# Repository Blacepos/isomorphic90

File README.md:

# Isomorphic 90: A Generic Keyboard and MIDI Controller
This project is licensed under the GNU GPLv3.

This is a prototype for a future larger board.

## Features
- 90 hex-shaped velocity-sensitive keys
- Per-key RGB
- QMK compatible

## Technical
- 180 switches
- MCU: STM32F405ZGT
- LED driver: IS313741A
- RGB matrix uses external 5V power. This might not be necessary here, but will be in the larger board.

You can view the PCBs and schematics on kicanvas.org:
- [board1](https://kicanvas.org/?github=https%3A%2F%2Fgithub.com%2FBlacepos%2Fisomorphic90%2Ftree%2Fmain%2Fboard1)
- [board2](https://kicanvas.org/?github=https%3A%2F%2Fgithub.com%2FBlacepos%2Fisomorphic90%2Ftree%2Fmain%2Fboard2)

## Status
Both PCBs are nearing completion. Firmware code will be added here when it is time to implement.

## Images
Board1

Board2

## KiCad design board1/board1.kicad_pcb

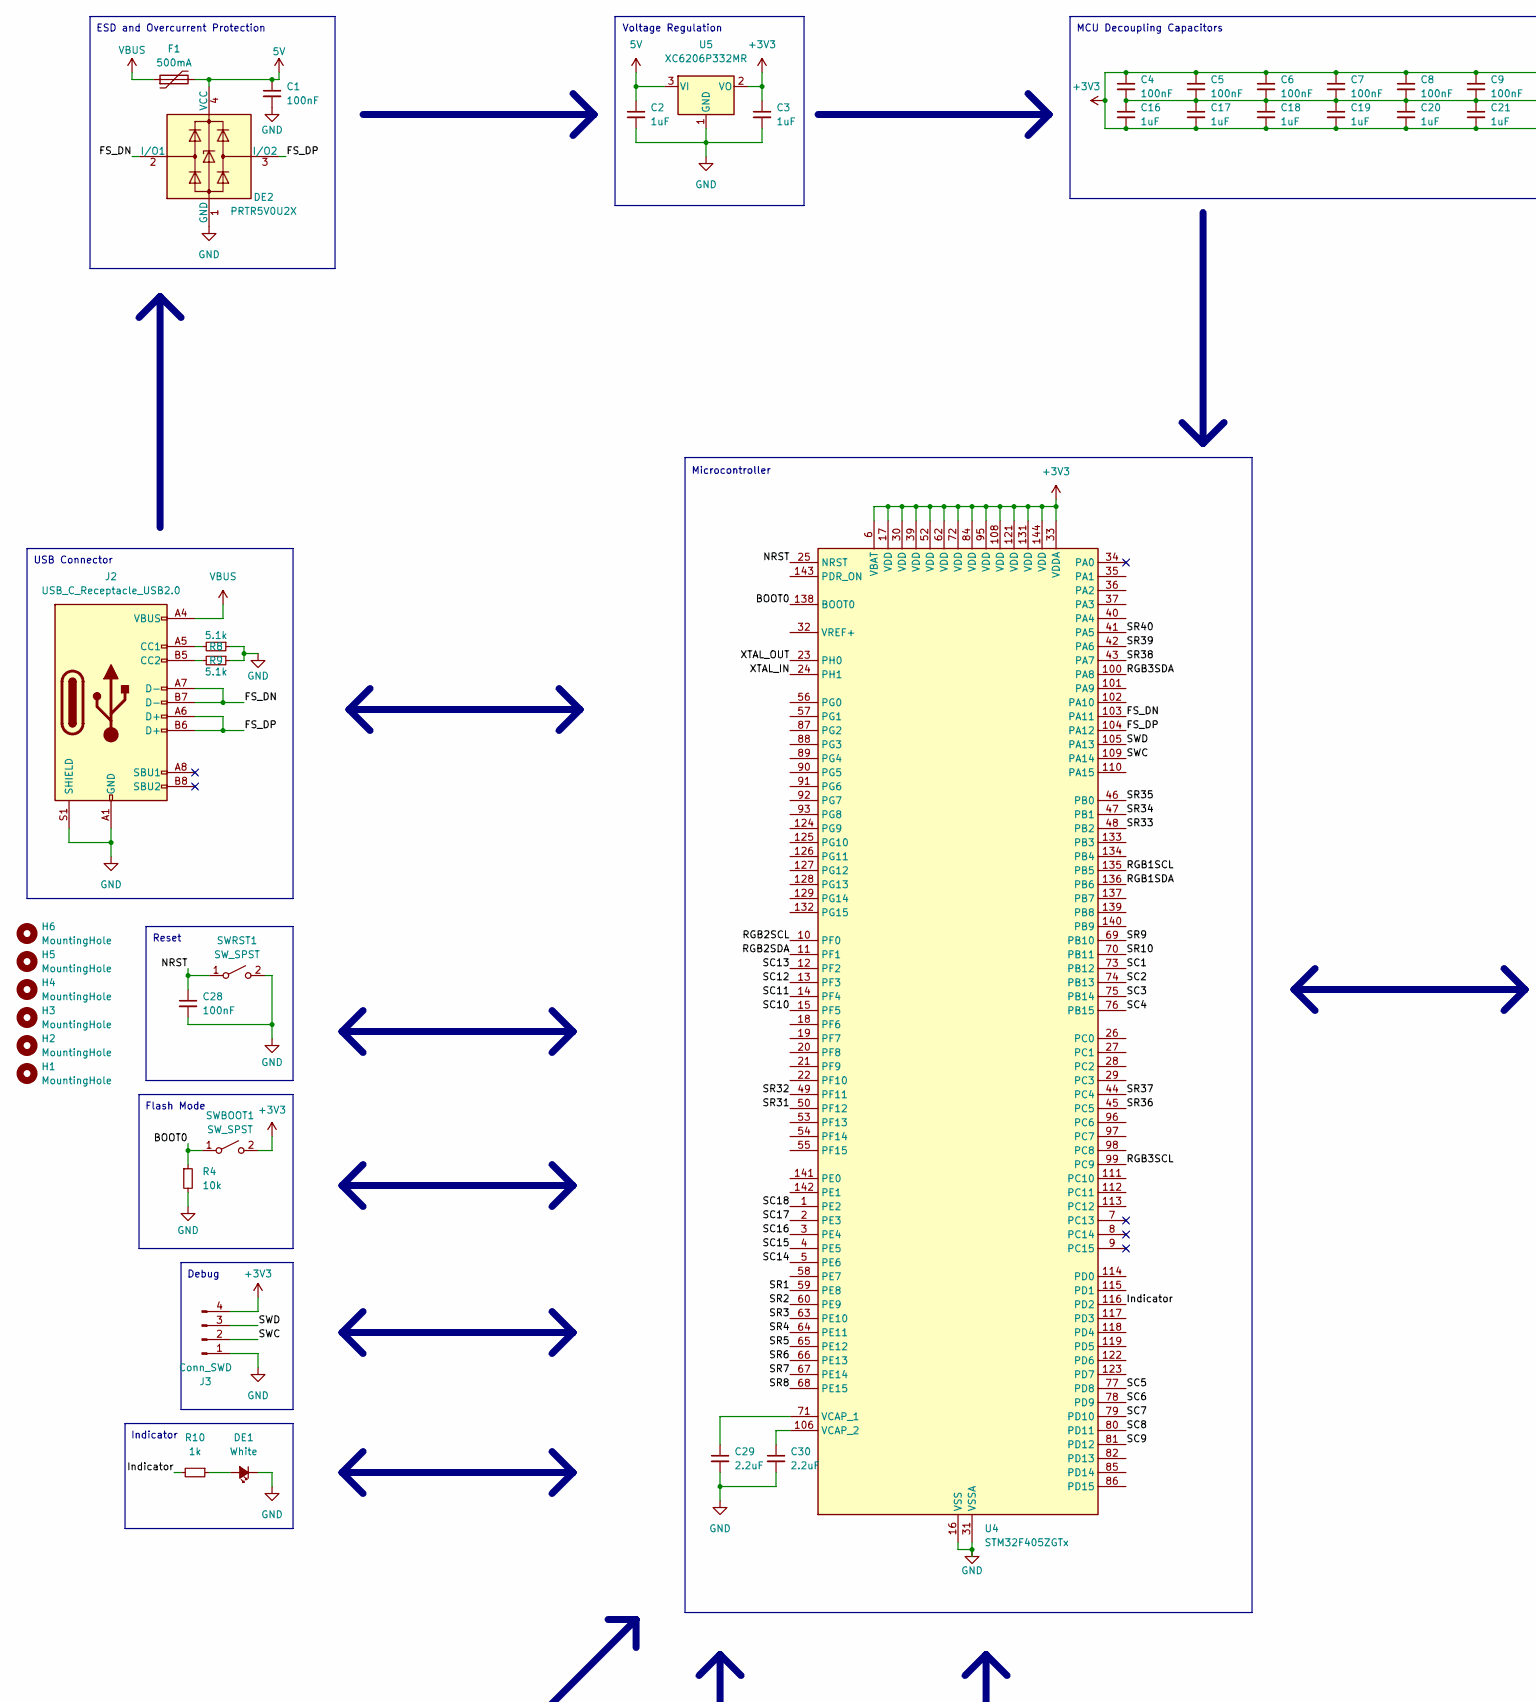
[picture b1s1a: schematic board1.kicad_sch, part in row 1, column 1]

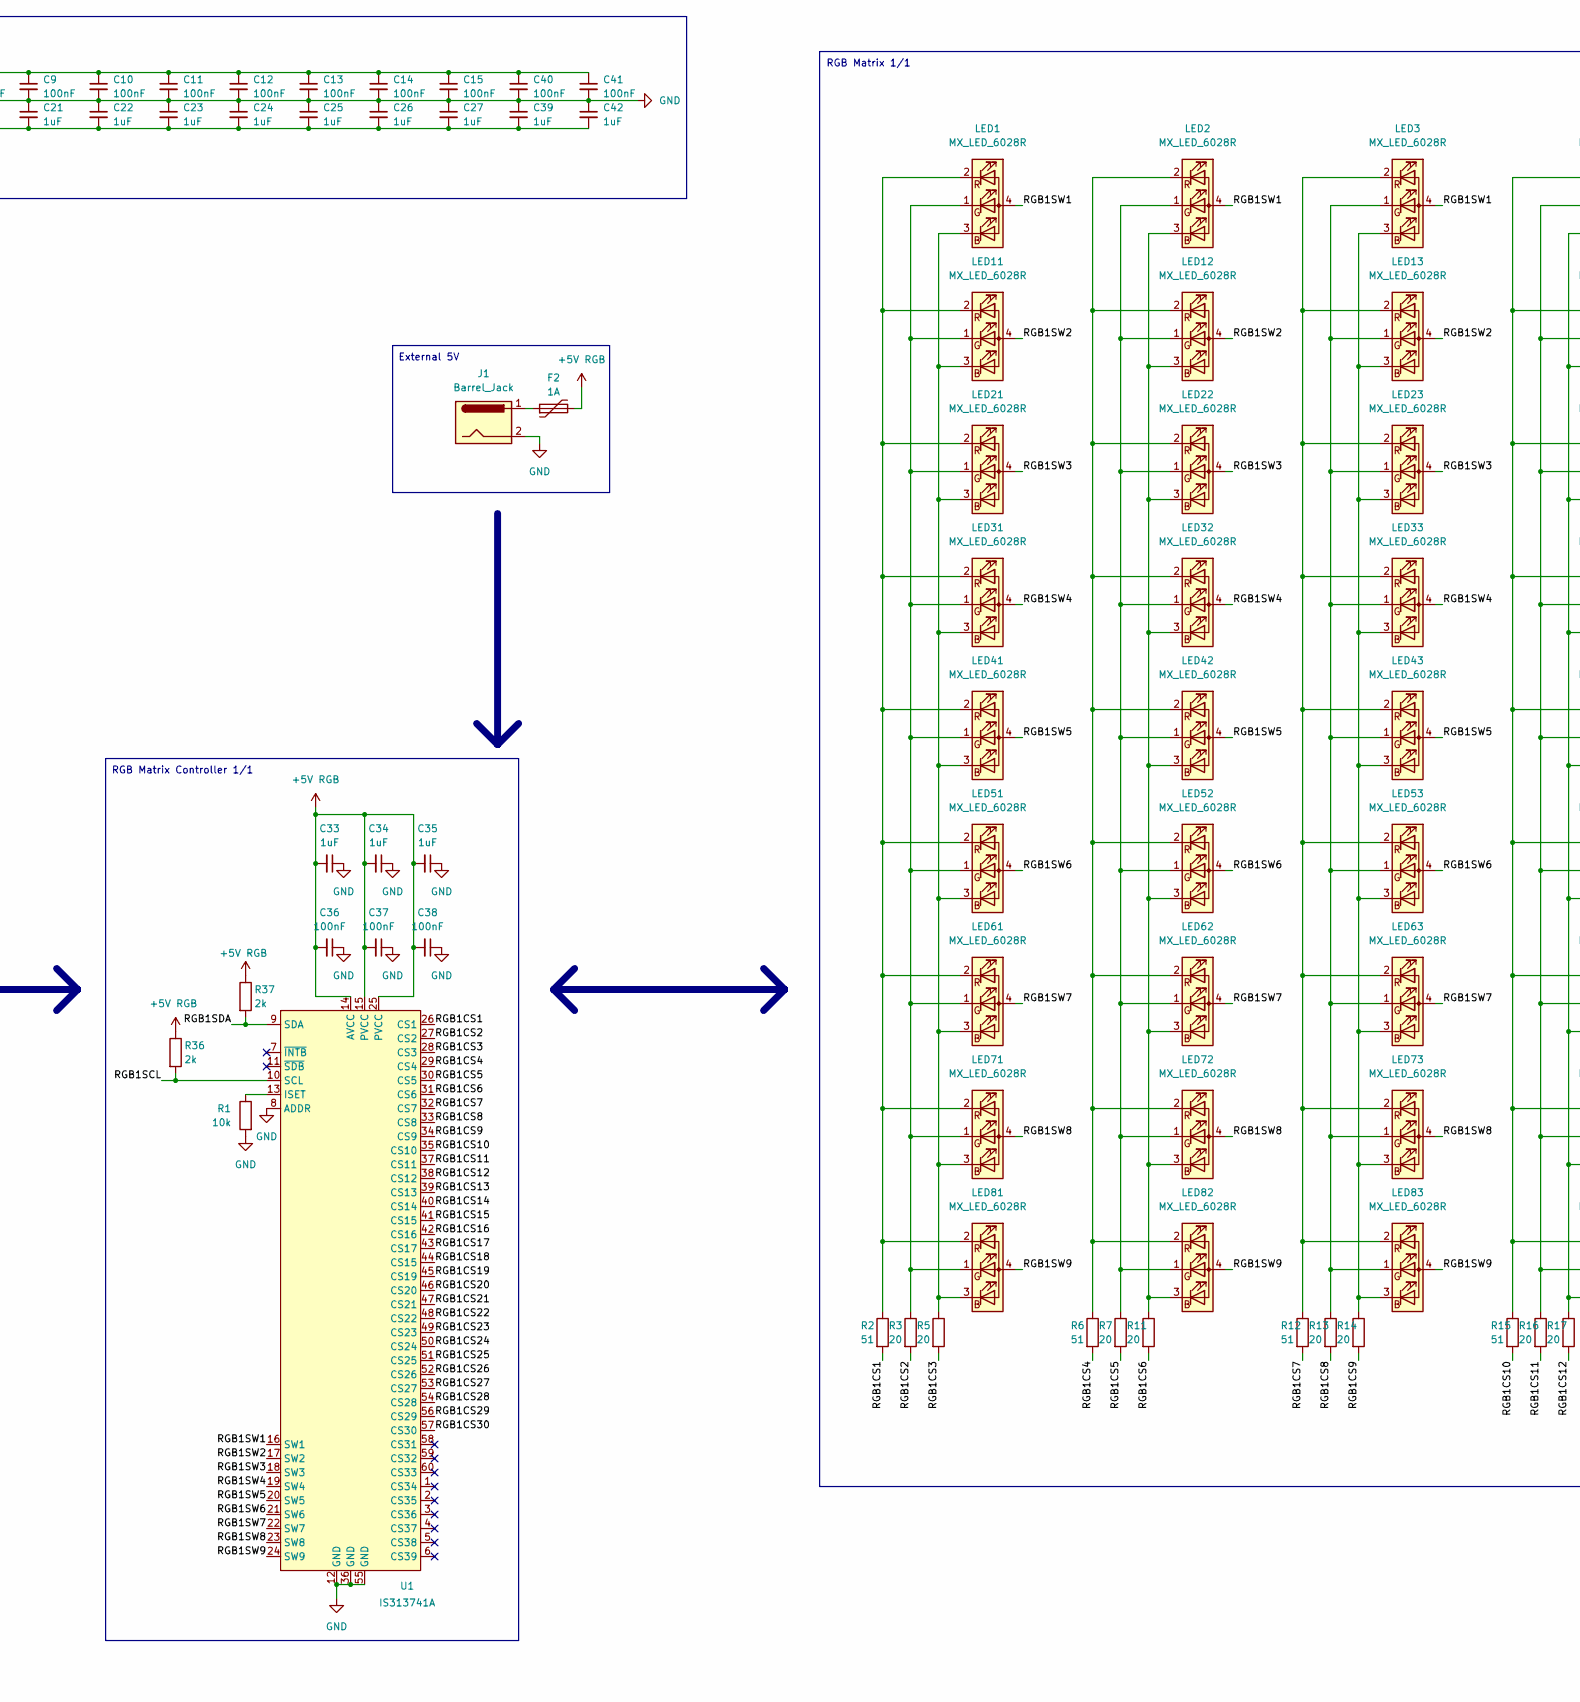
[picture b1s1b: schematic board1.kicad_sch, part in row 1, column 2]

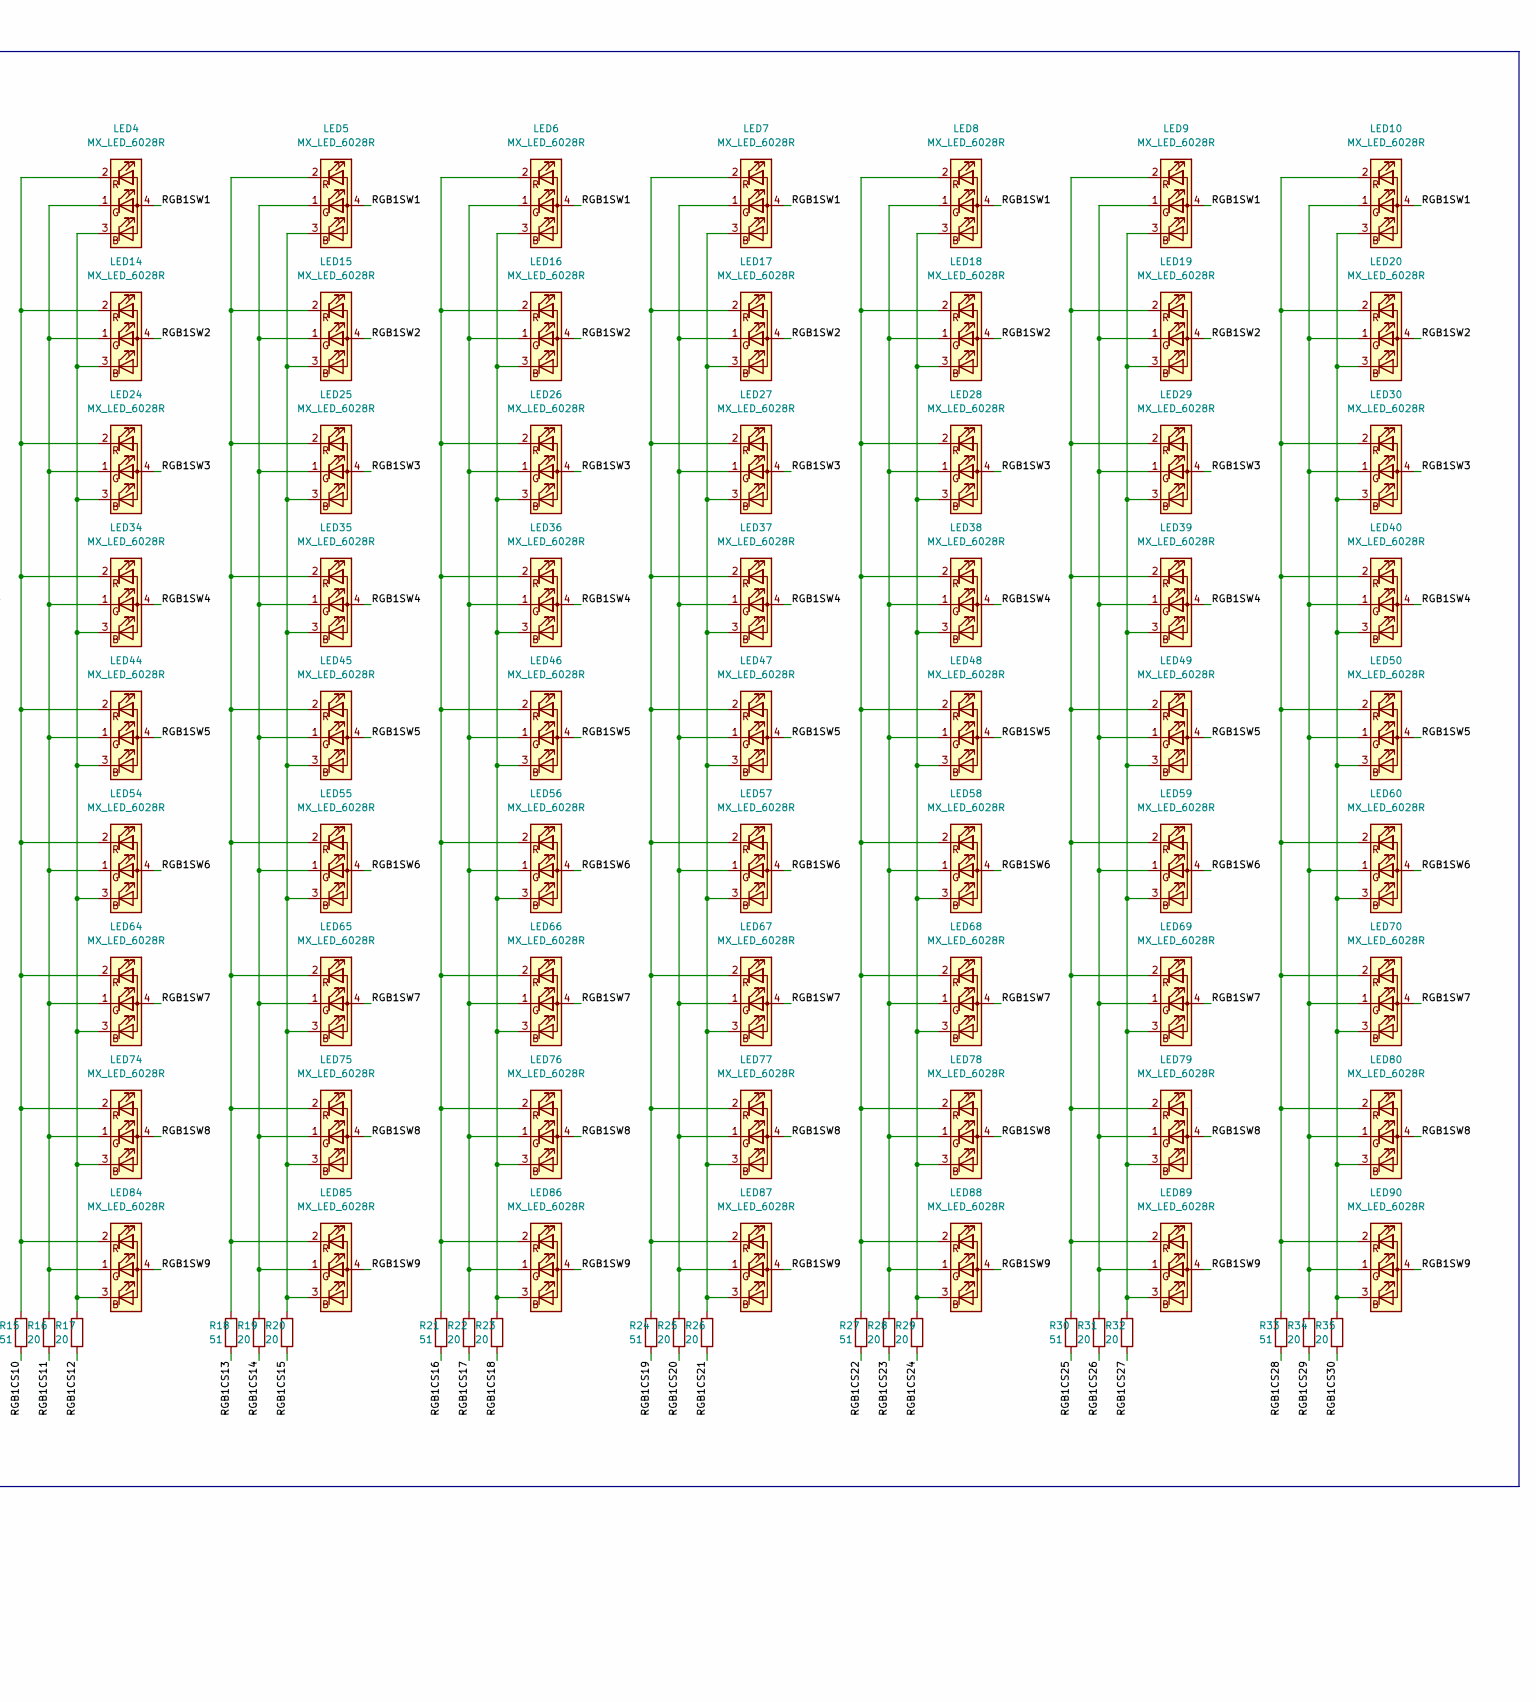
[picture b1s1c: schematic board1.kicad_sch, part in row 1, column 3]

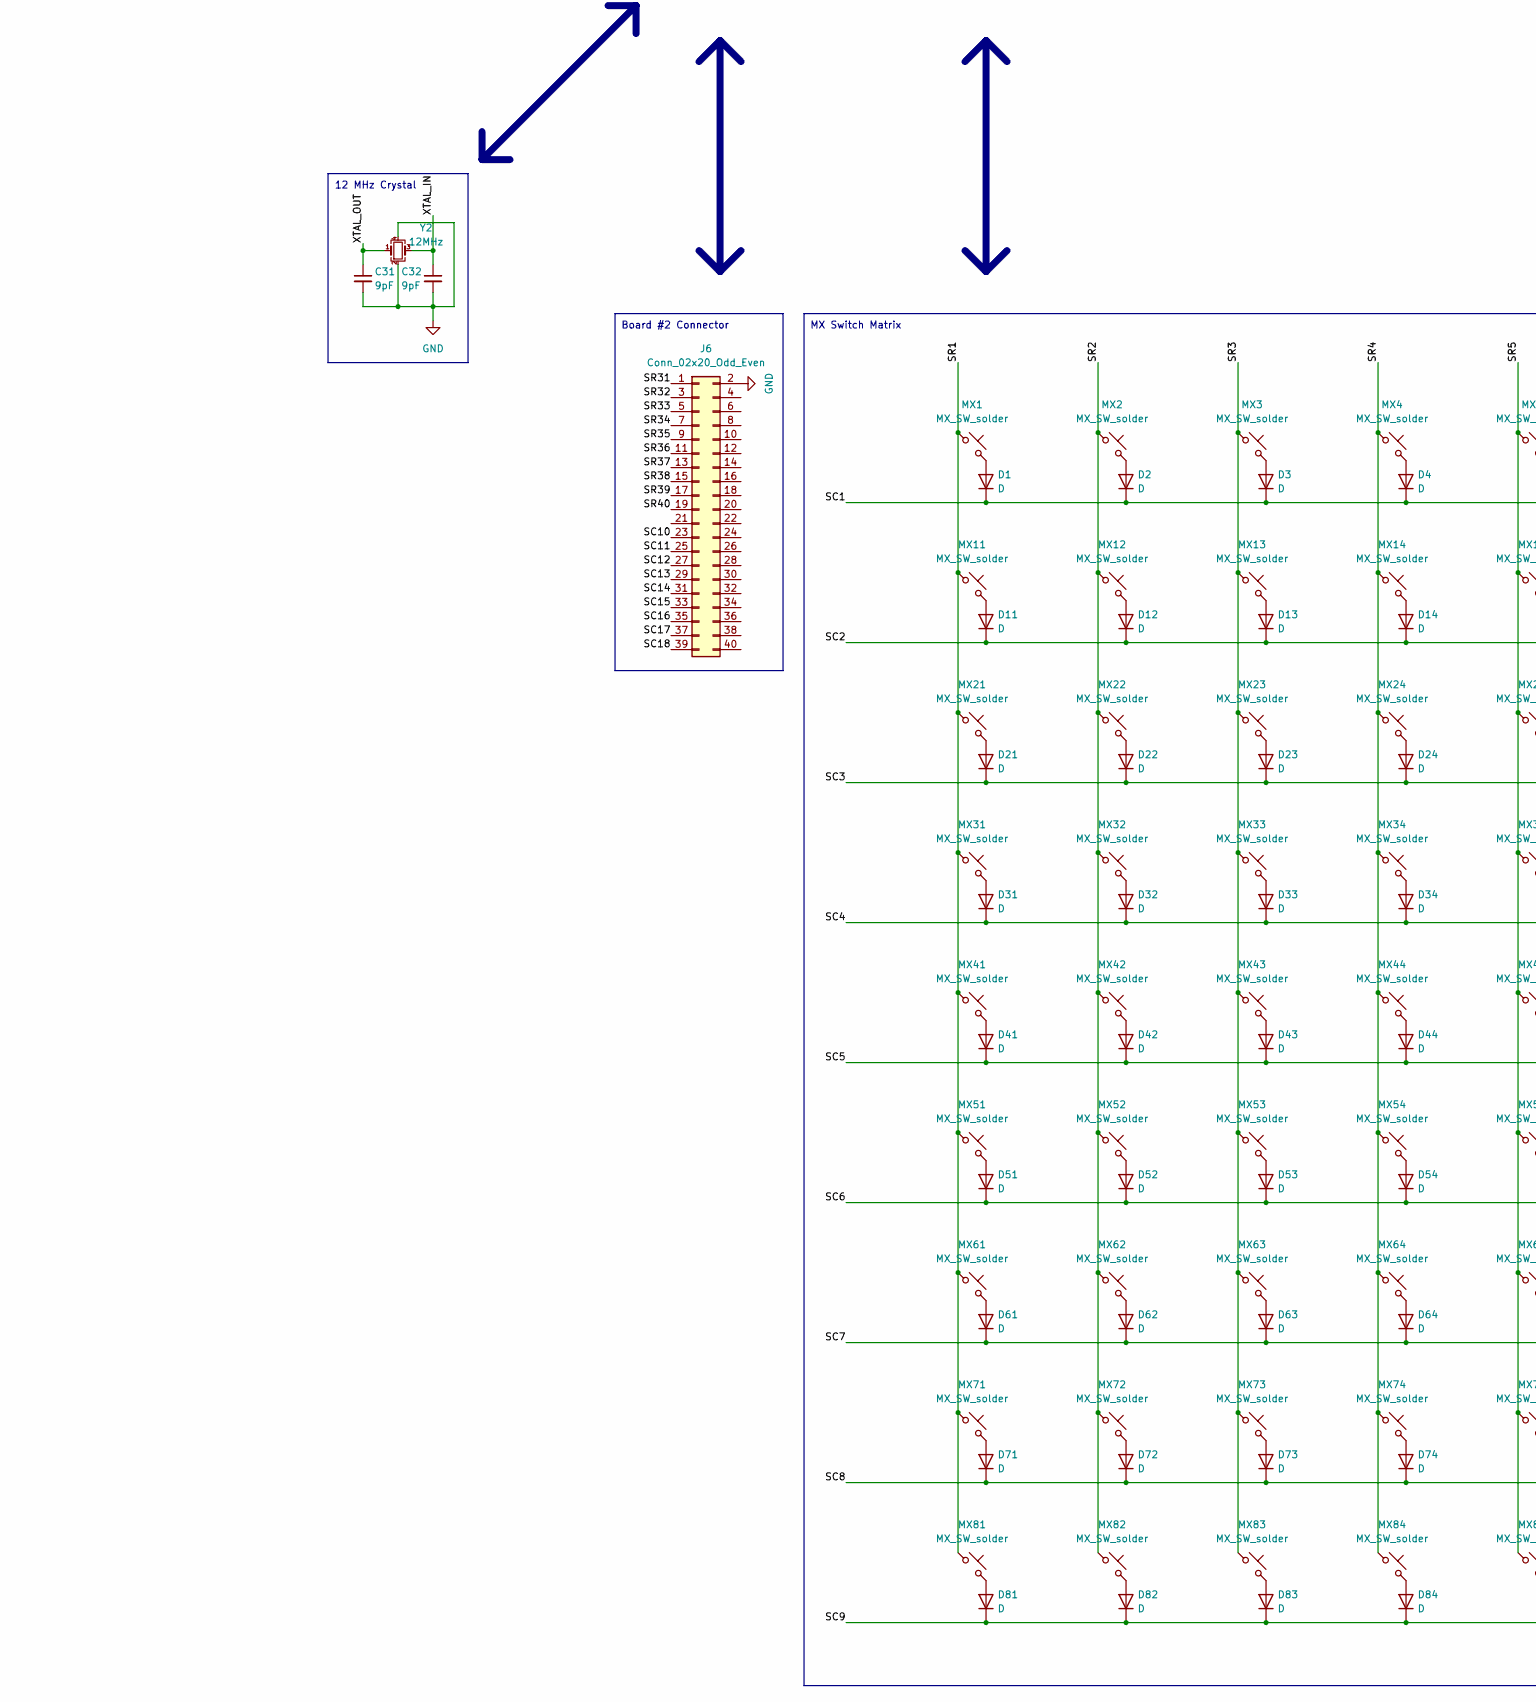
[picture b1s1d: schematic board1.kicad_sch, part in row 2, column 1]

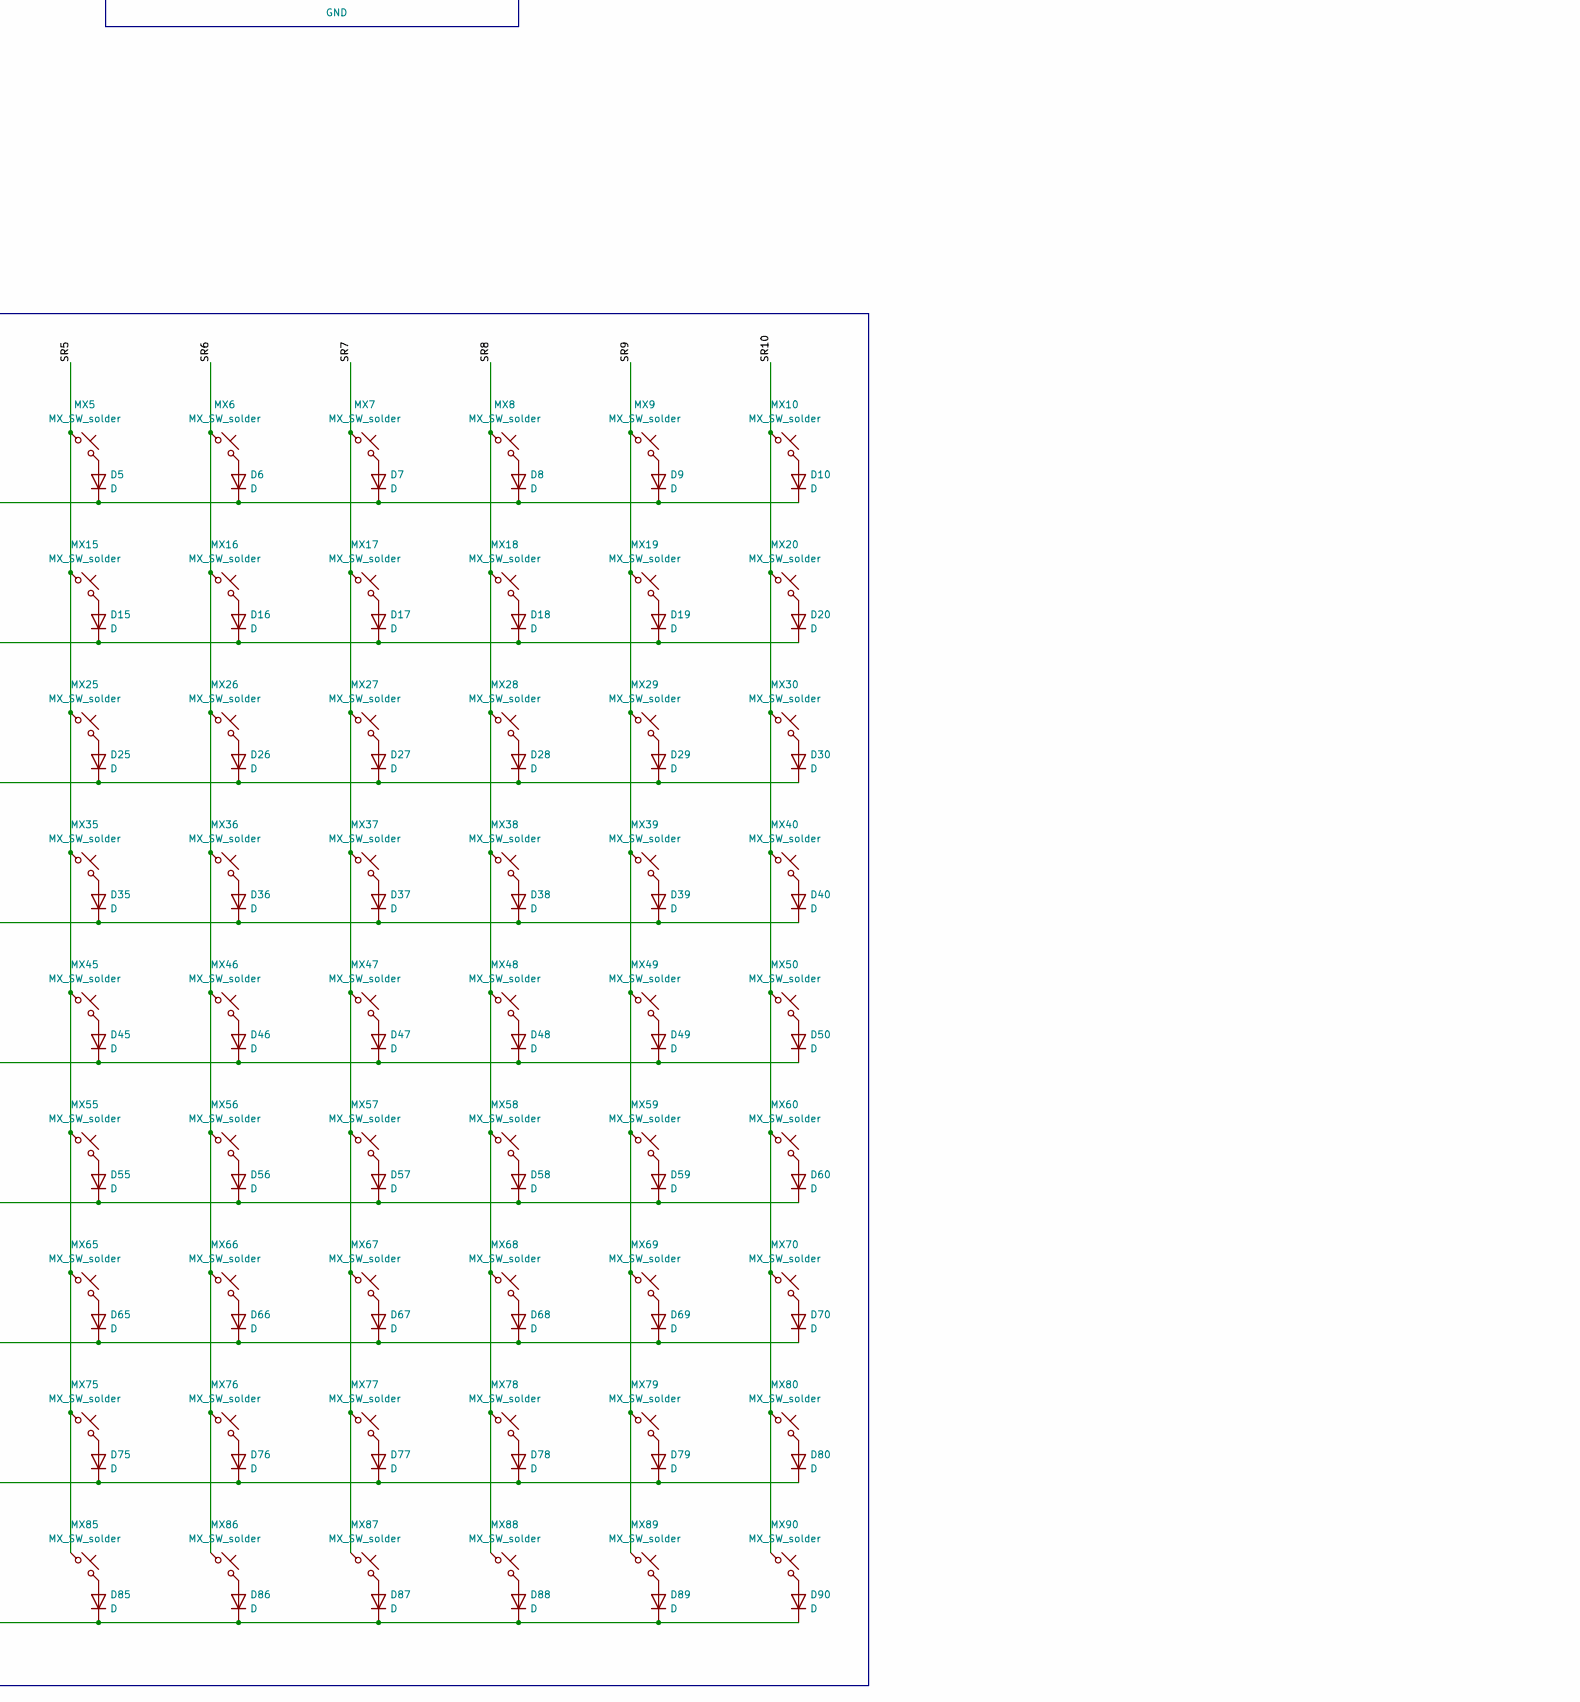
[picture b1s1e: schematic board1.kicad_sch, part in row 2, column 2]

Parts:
C1, C4, C5, C6, C7, C8, C9, C10, C11, C12, C13, C14, C15, C40, C41: 100nF; C_0603_1608Metric
C2, C3, C16, C17, C18, C19, C20, C21, C22, C23, C24, C25, C26, C27, C39, C42: 1uF; C_0603_1608Metric
C28, C36, C37, C38: 100nF; C_0402_1005Metric
C29, C30: 2.2uF; C_0603_1608Metric
C31, C32: 9pF; C_0402_1005Metric
C33, C34, C35: 1uF; C_0402_1005Metric
D1, D2, D3, D4, D5, D6, D7, D8, D9, D10, D11, D12, D13, D14, D15, D16, D17, D18, D19, D20, D21, D22, D23, D24, D25, D26, D27, D28, D29, D30, D31, D32, D33, D34, D35, D36, D37, D38, D39, D40, D41, D42, D43, D44, D45, D46, D47, D48, D49, D50, D51, D52, D53, D54, D55, D56, D57, D58, D59, D60, D61, D62, D63, D64, D65, D66, D67, D68, D69, D70, D71, D72, D73, D74, D75, D76, D77, D78, D79, D80, D81, D82, D83, D84, D85, D86, D87, D88, D89, D90: D; D_SOD-123
DE1: White; LED_0402_1005Metric
DE2: PRTR5V0U2X; SOT-143
F1: 500mA; Fuse_1206_3216Metric
F2: 1A; Fuse_1206_3216Metric
H1, H2, H3, H4, H5, H6: MountingHole; MountingHole_2.2mm_M2
J1: Barrel_Jack; BarrelJack_CUI_PJ-063AH_Horizontal
J2: USB_C_Receptacle_USB2.0; USB_C_Receptacle_HRO_TYPE-C-31-M-12
J3: Conn_SWD; PinHeader_1x04_P1.27mm_Vertical
J6: Conn_02x20_Odd_Even; IDC-Header_2x20_P2.54mm_Vertical
LED1, LED2, LED3, LED4, LED5, LED6, LED7, LED8, LED9, LED10, LED11, LED12, LED13, LED14, LED15, LED16, LED17, LED18, LED19, LED20, LED21, LED22, LED23, LED24, LED25, LED26, LED27, LED28, LED29, LED30, LED31, LED32, LED33, LED34, LED35, LED36, LED37, LED38, LED39, LED40, LED41, LED42, LED43, LED44, LED45, LED46, LED47, LED48, LED49, LED50, LED51, LED52, LED53, LED54, LED55, LED56, LED57, LED58, LED59, LED60, LED61, LED62, LED63, LED64, LED65, LED66, LED67, LED68, LED69, LED70, LED71, LED72, LED73, LED74, LED75, LED76, LED77, LED78, LED79, LED80, LED81, LED82, LED83, LED84, LED85, LED86, LED87, LED88, LED89, LED90: MX_LED_6028R; LED_MX_6028R_HEX_EDIT
MX1, MX2, MX3, MX4, MX5, MX6, MX7, MX8, MX9, MX10, MX11, MX12, MX13, MX14, MX15, MX16, MX17, MX18, MX19, MX20, MX21, MX22, MX23, MX24, MX25, MX26, MX27, MX28, MX29, MX30, MX31, MX32, MX33, MX34, MX35, MX36, MX37, MX38, MX39, MX40, MX41, MX42, MX43, MX44, MX45, MX46, MX47, MX48, MX49, MX50, MX51, MX52, MX53, MX54, MX55, MX56, MX57, MX58, MX59, MX60, MX61, MX62, MX63, MX64, MX65, MX66, MX67, MX68, MX69, MX70, MX71, MX72, MX73, MX74, MX75, MX76, MX77, MX78, MX79, MX80, MX81, MX82, MX83, MX84, MX85, MX86, MX87, MX88, MX89, MX90: MX_SW_solder; SW_MX_HEX_EDIT
R1, R4: 10k; R_0402_1005Metric
R2, R6, R12, R15, R18, R21, R24, R27, R30, R33: 51; R_0402_1005Metric
R3, R5, R7, R11, R13, R14, R16, R17, R19, R20, R22, R23, R25, R26, R28, R29, R31, R32, R34, R35: 20; R_0402_1005Metric
R8, R9: 5.1k; R_0402_1005Metric
R10: 1k; R_0402_1005Metric
R36, R37: 2k; R_0402_1005Metric
SWBOOT1: SW_SPST; SW_SPST_TL3342
SWRST1: SW_SPST; SW_SPST_TL3342
U1: IS313741A; QFN-60_EP_7x7_Pitch0.4mm
U4: STM32F405ZGTx; LQFP-144_20x20mm_P0.5mm
U5: XC6206P332MR; SOT-23
Y2: 12MHz; Crystal_SMD_3225-4Pin_3.2x2.5mm

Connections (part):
5V: C1.1, C2.1, DE2.4 (VCC), F1.2, U5.3 (VI)
+3V3: C3.1, C4.1, C5.1, C6.1, C7.1, C8.1, C9.1, C10.1, C11.1, C12.1, C13.1, C14.1, C15.1, C16.2, C17.2, C18.2, C19.2, C20.2, C21.2, C22.2, C23.2, C24.2, C25.2, C26.2, C27.2, C39.2, C40.1, C41.1, C42.2, J3.4, SWBOOT1.2 (B), U4.6 (VBAT), U4.17 (VDD), U4.30 (VDD), U4.33 (VDDA), U4.39 (VDD), U4.52 (VDD), U4.62 (VDD), U4.72 (VDD), U4.84 (VDD), U4.95 (VDD), U4.108 (VDD), U4.121 (VDD), U4.131 (VDD), U4.144 (VDD), U5.2 (VO)
+5V RGB: C33.2, C34.2, C35.2, C36.2, C37.2, C38.2, F2.2, R36.1, R37.1, U1.14 (AVCC), U1.15 (PVCC), U1.25 (PVCC)
/BOOT0: R4.1, SWBOOT1.1 (A), U4.138 (BOOT0)
/FS_DN: DE2.2 (I/O1), J2.A7 (D-), J2.B7 (D-), U4.103 (PA11)
/FS_DP: DE2.3 (I/O2), J2.A6 (D+), J2.B6 (D+), U4.104 (PA12)
/Indicator: R10.2, U4.116 (PD2)
/NRST: C28.1, SWRST1.1 (A), U4.25 (NRST)
/RGB1CS1: R2.2, U1.26 (CS1)
/RGB1CS2: R3.2, U1.27 (CS2)
/RGB1CS3: R5.2, U1.28 (CS3)
/RGB1CS4: R6.2, U1.29 (CS4)
/RGB1CS5: R7.2, U1.30 (CS5)
/RGB1CS6: R11.2, U1.31 (CS6)
/RGB1CS7: R12.2, U1.32 (CS7)
/RGB1CS8: R13.2, U1.33 (CS8)
/RGB1CS9: R14.2, U1.34 (CS9)
/RGB1CS10: R15.2, U1.35 (CS10)
/RGB1CS11: R16.2, U1.37 (CS11)
/RGB1CS12: R17.2, U1.38 (CS12)
/RGB1CS13: R18.2, U1.39 (CS13)
/RGB1CS14: R19.2, U1.40 (CS14)
/RGB1CS15: R20.2, U1.41 (CS15)
/RGB1CS16: R21.2, U1.42 (CS16)
/RGB1CS17: R22.2, U1.43 (CS17)
/RGB1CS18: R23.2, U1.44 (CS15)
/RGB1CS19: R24.2, U1.45 (CS19)
/RGB1CS20: R25.2, U1.46 (CS20)
/RGB1CS21: R26.2, U1.47 (CS21)
/RGB1CS22: R27.2, U1.48 (CS22)
/RGB1CS23: R28.2, U1.49 (CS23)
/RGB1CS24: R29.2, U1.50 (CS24)
/RGB1CS25: R30.2, U1.51 (CS25)
/RGB1CS26: R31.2, U1.52 (CS26)
/RGB1CS27: R32.2, U1.53 (CS27)
/RGB1CS28: R33.2, U1.54 (CS28)
/RGB1CS29: R34.2, U1.56 (CS29)
/RGB1CS30: R35.2, U1.57 (CS30)
/RGB1SCL: R36.2, U1.10 (SCL), U4.135 (PB5)
/RGB1SDA: R37.2, U1.9 (SDA), U4.136 (PB6)
/RGB1SW1: LED1.4 (A), LED2.4 (A), LED3.4 (A), LED4.4 (A), LED5.4 (A), LED6.4 (A), LED7.4 (A), LED8.4 (A), LED9.4 (A), LED10.4 (A), U1.16 (SW1)
/RGB1SW2: LED11.4 (A), LED12.4 (A), LED13.4 (A), LED14.4 (A), LED15.4 (A), LED16.4 (A), LED17.4 (A), LED18.4 (A), LED19.4 (A), LED20.4 (A), U1.17 (SW2)
/RGB1SW3: LED21.4 (A), LED22.4 (A), LED23.4 (A), LED24.4 (A), LED25.4 (A), LED26.4 (A), LED27.4 (A), LED28.4 (A), LED29.4 (A), LED30.4 (A), U1.18 (SW3)
/RGB1SW4: LED31.4 (A), LED32.4 (A), LED33.4 (A), LED34.4 (A), LED35.4 (A), LED36.4 (A), LED37.4 (A), LED38.4 (A), LED39.4 (A), LED40.4 (A), U1.19 (SW4)
/RGB1SW5: LED41.4 (A), LED42.4 (A), LED43.4 (A), LED44.4 (A), LED45.4 (A), LED46.4 (A), LED47.4 (A), LED48.4 (A), LED49.4 (A), LED50.4 (A), U1.20 (SW5)
/RGB1SW6: LED51.4 (A), LED52.4 (A), LED53.4 (A), LED54.4 (A), LED55.4 (A), LED56.4 (A), LED57.4 (A), LED58.4 (A), LED59.4 (A), LED60.4 (A), U1.21 (SW6)
/RGB1SW7: LED61.4 (A), LED62.4 (A), LED63.4 (A), LED64.4 (A), LED65.4 (A), LED66.4 (A), LED67.4 (A), LED68.4 (A), LED69.4 (A), LED70.4 (A), U1.22 (SW7)
/RGB1SW8: LED71.4 (A), LED72.4 (A), LED73.4 (A), LED74.4 (A), LED75.4 (A), LED76.4 (A), LED77.4 (A), LED78.4 (A), LED79.4 (A), LED80.4 (A), U1.23 (SW8)
/RGB1SW9: LED81.4 (A), LED82.4 (A), LED83.4 (A), LED84.4 (A), LED85.4 (A), LED86.4 (A), LED87.4 (A), LED88.4 (A), LED89.4 (A), LED90.4 (A), U1.24 (SW9)
/RGB2SCL: U4.10 (PF0)
/RGB2SDA: U4.11 (PF1)
/RGB3SCL: U4.99 (PC9)
/RGB3SDA: U4.100 (PA8)
/SC1: D1.1 (K), D2.1 (K), D3.1 (K), D4.1 (K), D5.1 (K), D6.1 (K), D7.1 (K), D8.1 (K), D9.1 (K), D10.1 (K), U4.73 (PB12)
/SC2: D11.1 (K), D12.1 (K), D13.1 (K), D14.1 (K), D15.1 (K), D16.1 (K), D17.1 (K), D18.1 (K), D19.1 (K), D20.1 (K), U4.74 (PB13)
/SC3: D21.1 (K), D22.1 (K), D23.1 (K), D24.1 (K), D25.1 (K), D26.1 (K), D27.1 (K), D28.1 (K), D29.1 (K), D30.1 (K), U4.75 (PB14)
/SC4: D31.1 (K), D32.1 (K), D33.1 (K), D34.1 (K), D35.1 (K), D36.1 (K), D37.1 (K), D38.1 (K), D39.1 (K), D40.1 (K), U4.76 (PB15)
/SC5: D41.1 (K), D42.1 (K), D43.1 (K), D44.1 (K), D45.1 (K), D46.1 (K), D47.1 (K), D48.1 (K), D49.1 (K), D50.1 (K), U4.77 (PD8)
/SC6: D51.1 (K), D52.1 (K), D53.1 (K), D54.1 (K), D55.1 (K), D56.1 (K), D57.1 (K), D58.1 (K), D59.1 (K), D60.1 (K), U4.78 (PD9)
/SC7: D61.1 (K), D62.1 (K), D63.1 (K), D64.1 (K), D65.1 (K), D66.1 (K), D67.1 (K), D68.1 (K), D69.1 (K), D70.1 (K), U4.79 (PD10)
/SC8: D71.1 (K), D72.1 (K), D73.1 (K), D74.1 (K), D75.1 (K), D76.1 (K), D77.1 (K), D78.1 (K), D79.1 (K), D80.1 (K), U4.80 (PD11)
/SC9: D81.1 (K), D82.1 (K), D83.1 (K), D84.1 (K), D85.1 (K), D86.1 (K), D87.1 (K), D88.1 (K), D89.1 (K), D90.1 (K), U4.81 (PD12)
/SC10: J6.23, U4.15 (PF5)
/SC11: J6.25, U4.14 (PF4)
/SC12: J6.27, U4.13 (PF3)
/SC13: J6.29, U4.12 (PF2)
/SC14: J6.31, U4.5 (PE6)
/SC15: J6.33, U4.4 (PE5)
/SC16: J6.35, U4.3 (PE4)
/SC17: J6.37, U4.2 (PE3)
/SC18: J6.39, U4.1 (PE2)
/SR1: MX1.1, MX11.1, MX21.1, MX31.1, MX41.1, MX51.1, MX61.1, MX71.1, MX81.1, U4.59 (PE8)
/SR2: MX2.1, MX12.1, MX22.1, MX32.1, MX42.1, MX52.1, MX62.1, MX72.1, MX82.1, U4.60 (PE9)
/SR3: MX3.1, MX13.1, MX23.1, MX33.1, MX43.1, MX53.1, MX63.1, MX73.1, MX83.1, U4.63 (PE10)
/SR4: MX4.1, MX14.1, MX24.1, MX34.1, MX44.1, MX54.1, MX64.1, MX74.1, MX84.1, U4.64 (PE11)
/SR5: MX5.1, MX15.1, MX25.1, MX35.1, MX45.1, MX55.1, MX65.1, MX75.1, MX85.1, U4.65 (PE12)
/SR6: MX6.1, MX16.1, MX26.1, MX36.1, MX46.1, MX56.1, MX66.1, MX76.1, MX86.1, U4.66 (PE13)
/SR7: MX7.1, MX17.1, MX27.1, MX37.1, MX47.1, MX57.1, MX67.1, MX77.1, MX87.1, U4.67 (PE14)
/SR8: MX8.1, MX18.1, MX28.1, MX38.1, MX48.1, MX58.1, MX68.1, MX78.1, MX88.1, U4.68 (PE15)
/SR9: MX9.1, MX19.1, MX29.1, MX39.1, MX49.1, MX59.1, MX69.1, MX79.1, MX89.1, U4.69 (PB10)
/SR10: MX10.1, MX20.1, MX30.1, MX40.1, MX50.1, MX60.1, MX70.1, MX80.1, MX90.1, U4.70 (PB11)
/SR31: J6.1, U4.50 (PF12)
/SR32: J6.3, U4.49 (PF11)
/SR33: J6.5, U4.48 (PB2)
/SR34: J6.7, U4.47 (PB1)
/SR35: J6.9, U4.46 (PB0)
/SR36: J6.11, U4.45 (PC5)
/SR37: J6.13, U4.44 (PC4)
/SR38: J6.15, U4.43 (PA7)
/SR39: J6.17, U4.42 (PA6)
/SR40: J6.19, U4.41 (PA5)
/SWC: J3.2, U4.109 (PA14)
/SWD: J3.3, U4.105 (PA13)
/XTAL_IN: C32.1, U4.24 (PH1), Y2.3
/XTAL_OUT: C31.1, U4.23 (PH0), Y2.1
GND: C1.2, C2.2, C3.2, C4.2, C5.2, C6.2, C7.2, C8.2, C9.2, C10.2, C11.2, C12.2, C13.2, C14.2, C15.2, C16.1, C17.1, C18.1, C19.1, C20.1, C21.1, C22.1, C23.1, C24.1, C25.1, C26.1, C27.1, C28.2, C29.2, C30.2, C31.2, C32.2, C33.1, C34.1, C35.1, C36.1, C37.1, C38.1, C39.1, C40.2, C41.2, C42.1, DE1.1 (K), DE2.1 (GND), J1.2, J2.A1 (GND), J2.A12 (GND), J2.B1 (GND), J2.B12 (GND), J2.S1 (SHIELD), J3.1, J6.2, R1.2, R4.2, R8.1, R9.1, SWRST1.2 (B), U1.8 (ADDR), U1.12 (GND), U1.36 (GND), U1.55 (GND), U1.61 (GND), U4.16 (VSS), U4.31 (VSSA), U4.38 (VSS), U4.51 (VSS), U4.61 (VSS), U4.83 (VSS), U4.94 (VSS), U4.107 (VSS), U4.120 (VSS), U4.130 (VSS), U5.1 (GND), Y2.2, Y2.4
unnamed: D1.2 (A), MX1.2
unnamed: D2.2 (A), MX2.2
unnamed: D3.2 (A), MX3.2
unnamed: D4.2 (A), MX4.2
unnamed: D5.2 (A), MX5.2
unnamed: D6.2 (A), MX6.2
unnamed: D7.2 (A), MX7.2
unnamed: D8.2 (A), MX8.2
unnamed: D9.2 (A), MX9.2
unnamed: D10.2 (A), MX10.2
unnamed: D11.2 (A), MX11.2
unnamed: D12.2 (A), MX12.2
unnamed: D13.2 (A), MX13.2
unnamed: D14.2 (A), MX14.2
unnamed: D15.2 (A), MX15.2
unnamed: D16.2 (A), MX16.2
unnamed: D17.2 (A), MX17.2
unnamed: D18.2 (A), MX18.2
unnamed: D19.2 (A), MX19.2
unnamed: D20.2 (A), MX20.2
unnamed: D21.2 (A), MX21.2
unnamed: D22.2 (A), MX22.2
unnamed: D23.2 (A), MX23.2
unnamed: D24.2 (A), MX24.2
unnamed: D25.2 (A), MX25.2
unnamed: D26.2 (A), MX26.2
unnamed: D27.2 (A), MX27.2
unnamed: D28.2 (A), MX28.2
unnamed: D29.2 (A), MX29.2
unnamed: D30.2 (A), MX30.2
unnamed: D31.2 (A), MX31.2
unnamed: D32.2 (A), MX32.2
unnamed: D33.2 (A), MX33.2
unnamed: D34.2 (A), MX34.2
unnamed: D35.2 (A), MX35.2
unnamed: D36.2 (A), MX36.2
unnamed: D37.2 (A), MX37.2
unnamed: D38.2 (A), MX38.2
unnamed: D39.2 (A), MX39.2
unnamed: D40.2 (A), MX40.2
unnamed: D41.2 (A), MX41.2
unnamed: D42.2 (A), MX42.2
unnamed: D43.2 (A), MX43.2
unnamed: D44.2 (A), MX44.2
unnamed: D45.2 (A), MX45.2
unnamed: D46.2 (A), MX46.2
unnamed: D47.2 (A), MX47.2
unnamed: D48.2 (A), MX48.2
unnamed: D49.2 (A), MX49.2
unnamed: D50.2 (A), MX50.2
unnamed: D51.2 (A), MX51.2
unnamed: D52.2 (A), MX52.2
unnamed: D53.2 (A), MX53.2
unnamed: D54.2 (A), MX54.2
unnamed: D55.2 (A), MX55.2
unnamed: D56.2 (A), MX56.2
unnamed: D57.2 (A), MX57.2
unnamed: D58.2 (A), MX58.2
unnamed: D59.2 (A), MX59.2
unnamed: D60.2 (A), MX60.2
unnamed: D61.2 (A), MX61.2
unnamed: D62.2 (A), MX62.2
unnamed: D63.2 (A), MX63.2
unnamed: D64.2 (A), MX64.2
unnamed: D65.2 (A), MX65.2
unnamed: D66.2 (A), MX66.2
unnamed: D67.2 (A), MX67.2
unnamed: D68.2 (A), MX68.2
unnamed: D69.2 (A), MX69.2
unnamed: D70.2 (A), MX70.2
unnamed: D71.2 (A), MX71.2
unnamed: D72.2 (A), MX72.2
unnamed: D73.2 (A), MX73.2
unnamed: D74.2 (A), MX74.2
unnamed: D75.2 (A), MX75.2
unnamed: D76.2 (A), MX76.2
unnamed: D77.2 (A), MX77.2
unnamed: D78.2 (A), MX78.2
unnamed: D79.2 (A), MX79.2
unnamed: D80.2 (A), MX80.2
unnamed: D81.2 (A), MX81.2
unnamed: D82.2 (A), MX82.2
unnamed: D83.2 (A), MX83.2
unnamed: D84.2 (A), MX84.2
unnamed: D85.2 (A), MX85.2
unnamed: D86.2 (A), MX86.2
unnamed: D87.2 (A), MX87.2
unnamed: D88.2 (A), MX88.2
unnamed: D89.2 (A), MX89.2
unnamed: D90.2 (A), MX90.2
unnamed: DE1.2 (A), R10.1
unnamed: F2.1, J1.1
unnamed: J2.A5 (CC1), R8.2
unnamed: J2.B5 (CC2), R9.2
unnamed: LED1.3 (BK), LED11.3 (BK), LED21.3 (BK), LED31.3 (BK), LED41.3 (BK), LED51.3 (BK), LED61.3 (BK), LED71.3 (BK), LED81.3 (BK), R5.1
unnamed: LED1.1 (GK), LED11.1 (GK), LED21.1 (GK), LED31.1 (GK), LED41.1 (GK), LED51.1 (GK), LED61.1 (GK), LED71.1 (GK), LED81.1 (GK), R3.1
unnamed: LED1.2 (RK), LED11.2 (RK), LED21.2 (RK), LED31.2 (RK), LED41.2 (RK), LED51.2 (RK), LED61.2 (RK), LED71.2 (RK), LED81.2 (RK), R2.1
unnamed: LED10.3 (BK), LED20.3 (BK), LED30.3 (BK), LED40.3 (BK), LED50.3 (BK), LED60.3 (BK), LED70.3 (BK), LED80.3 (BK), LED90.3 (BK), R35.1
unnamed: LED10.1 (GK), LED20.1 (GK), LED30.1 (GK), LED40.1 (GK), LED50.1 (GK), LED60.1 (GK), LED70.1 (GK), LED80.1 (GK), LED90.1 (GK), R34.1
unnamed: LED10.2 (RK), LED20.2 (RK), LED30.2 (RK), LED40.2 (RK), LED50.2 (RK), LED60.2 (RK), LED70.2 (RK), LED80.2 (RK), LED90.2 (RK), R33.1
unnamed: LED2.3 (BK), LED12.3 (BK), LED22.3 (BK), LED32.3 (BK), LED42.3 (BK), LED52.3 (BK), LED62.3 (BK), LED72.3 (BK), LED82.3 (BK), R11.1
unnamed: LED2.1 (GK), LED12.1 (GK), LED22.1 (GK), LED32.1 (GK), LED42.1 (GK), LED52.1 (GK), LED62.1 (GK), LED72.1 (GK), LED82.1 (GK), R7.1
unnamed: LED2.2 (RK), LED12.2 (RK), LED22.2 (RK), LED32.2 (RK), LED42.2 (RK), LED52.2 (RK), LED62.2 (RK), LED72.2 (RK), LED82.2 (RK), R6.1
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
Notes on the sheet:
Indicator
MCU Decoupling Capacitors
External 5V
Board #2 Connector
USB Connector
RGB Matrix Controller 1/1
12 MHz Crystal
ESD and Overcurrent Protection
Debug
Microcontroller
RGB Matrix 1/1
Reset
Voltage Regulation
MX Switch Matrix
Flash Mode

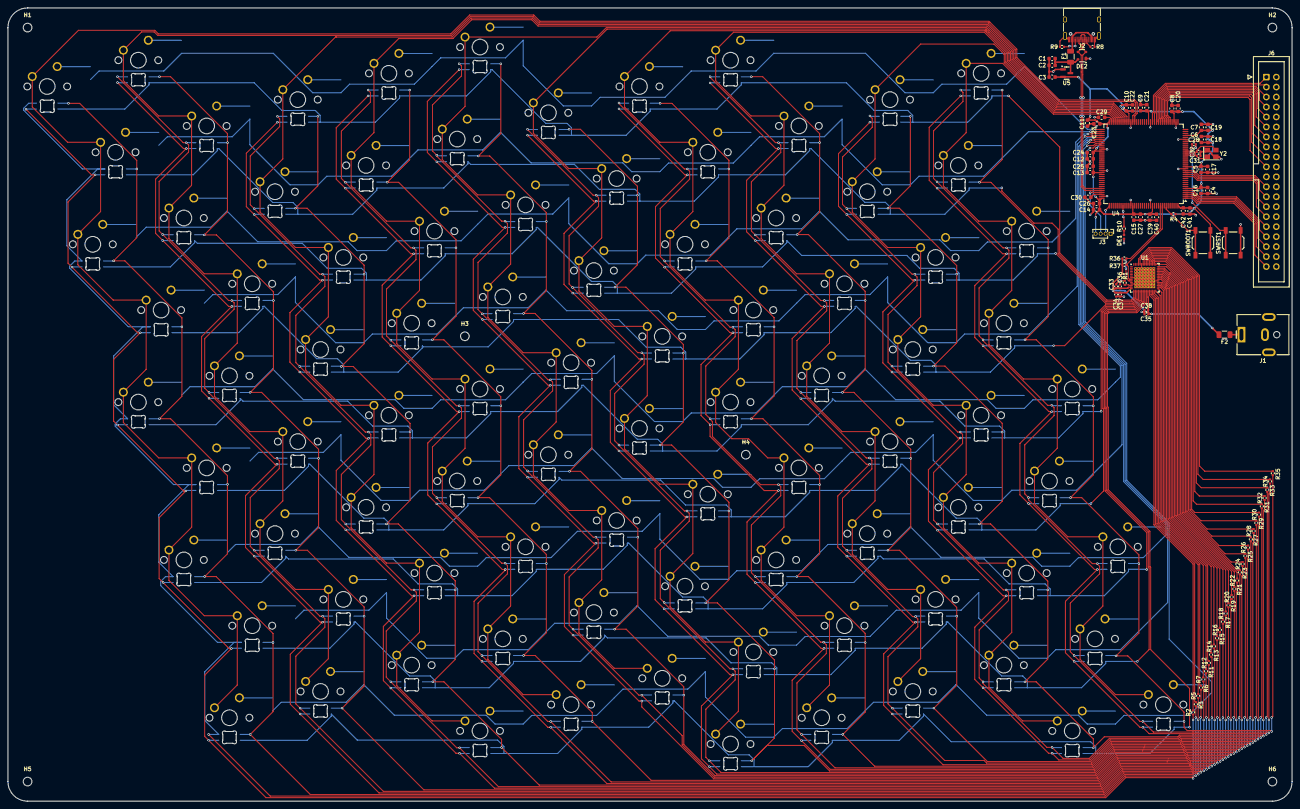
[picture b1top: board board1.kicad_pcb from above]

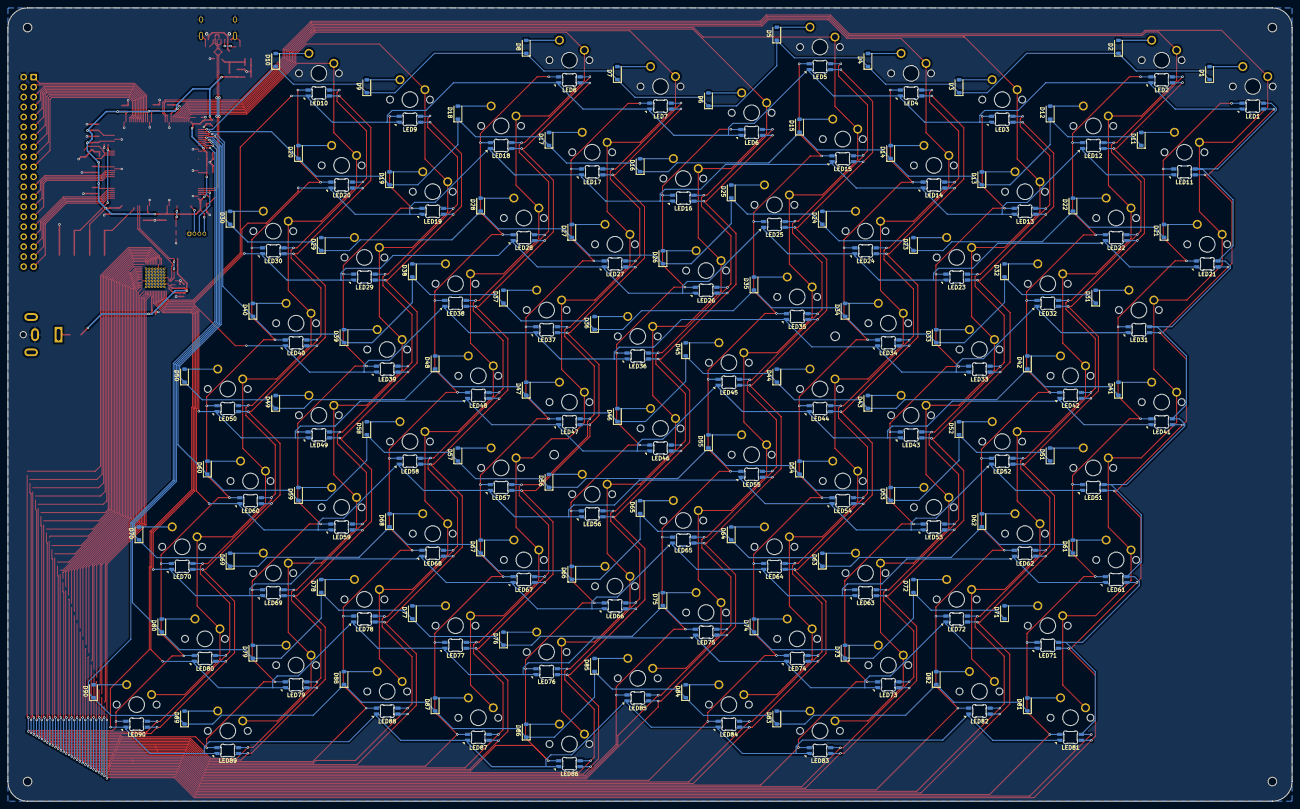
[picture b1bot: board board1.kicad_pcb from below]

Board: 2 copper layers, 327.0 x 202.0 mm, 369 parts (180 on the bottom side), 220 nets.
